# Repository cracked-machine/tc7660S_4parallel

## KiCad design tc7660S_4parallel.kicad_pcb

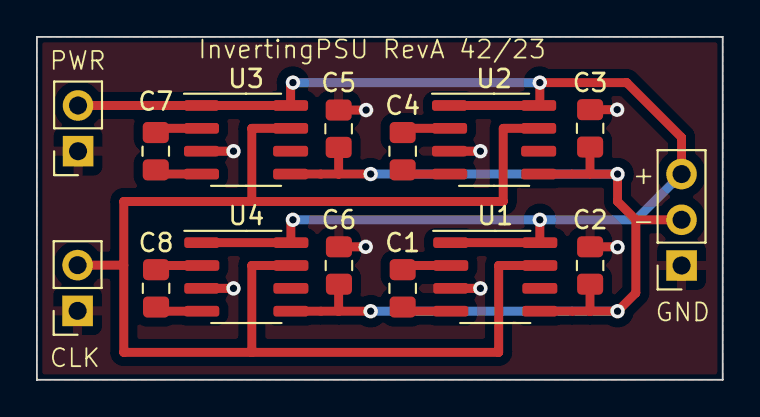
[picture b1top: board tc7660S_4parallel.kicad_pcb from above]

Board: 2 copper layers, 38.1 x 19.0 mm, 19 parts (0 on the bottom side), 16 nets.

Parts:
C1, C2, C3, C4, C5, C6, C7, C8: 10uF; C_0805_2012Metric_Pad1.18x1.45mm_HandSolder
J1: Conn_PowerIn; PinSocket_1x02_P2.54mm_Vertical
J3: Conn_ClockIn; PinSocket_1x02_P2.54mm_Vertical
J4: Conn_PowerOut; PinSocket_1x03_P2.54mm_Vertical
NT1, NT2, NT3, NT4: NetTie_2; NetTie-2_SMD_Pad0.5mm
U1, U2, U3, U4: TC7660SE0A; SOIC-8_3.9x4.9mm_P1.27mm

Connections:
/clk_c: J3.2, U1.7 (OSC), U2.7 (OSC), U3.7 (OSC), U4.7 (OSC)
/vinp_c: J1.2, J4.3, U1.1 (BOOST), U1.8 (V+), U2.1 (BOOST), U2.8 (V+), U3.1 (BOOST), U3.8 (V+), U4.1 (BOOST), U4.8 (V+)
/voutn_c: C2.1, C3.1, C5.1, C6.1, J4.2, NT1.2, NT2.2, NT3.2, NT4.2
GND: C2.2, C3.2, C5.2, C6.2, J1.1, J3.1, J4.1, U1.3 (GND), U2.3 (GND), U3.3 (GND), U4.3 (GND)
unnamed: C1.1, U1.2 (CAP+)
unnamed: C1.2, U1.4 (CAP-)
unnamed: NT1.1, U1.5 (VOUT)
unnamed: C4.1, U2.2 (CAP+)
unnamed: C4.2, U2.4 (CAP-)
unnamed: NT2.1, U2.5 (VOUT)
unnamed: C7.1, U3.2 (CAP+)
unnamed: C7.2, U3.4 (CAP-)
unnamed: NT3.1, U3.5 (VOUT)
unnamed: C8.1, U4.2 (CAP+)
unnamed: C8.2, U4.4 (CAP-)
unnamed: NT4.1, U4.5 (VOUT)

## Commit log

2023-10-18 reva
